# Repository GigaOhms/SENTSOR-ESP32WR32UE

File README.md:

# Learn KiCad Through a ESP32-micro Compact PCB Design Project

This repository is a learning resource to explore **PCB design with KiCad** through a practical project: a compact and powerful ESP32-based board.  
The reference for this project comes from [Sentsor Core ESP32-Micro](https://oshwlab.com/sentsor-project/sentsor-core-esp32-micro).

---

## Project Image

---

## Description

- **Super compact & powerful**, measured only 35.56x35.56mm (1400x1400mil) with 3x10P standard pitch 2.54mm (100mil) pinout, packing all the onboard features.  
- **ESP32-WROOM-32UE**, comes with latest ECO V3 Dual Core 32-bit LX6 microprocessor with clock up to 240MHz, ULP co-processor, 520kB SRAM, 16MB flash.  
- **802.11b/g/n WiFi Connectivity**, support mode STA/AP/STA+AP mode with external antenna using U.FL/IPEX connector allowing the board to be installed inside the enclosure without worrying transceiver signal quality.  
- **Bluetooth 4.2 Connectivity**, support classic bluetooth and Low Energy (LE) protocol.  
- **CP2104 UART to USB Bridge**, full-speed programmer & data port with auto-reset trigger using DTR and RTS line.  
- **DS3231M RTC**, extremely accurate ±5ppm RTC with alarm trigger capability and onboard MS621FE rechargeable backup battery. Connected via I2C at address 0x68.  
- **Battery Powered**, run SENTSOR board everywhere without power supply issue with 1-cell Lithium Ion/Polymer battery via JST-PH connector.  
- **CN3165 Battery Charger**, solar-powered and USB-compatible Lithium Ion/Polymer charger with on-chip adaptive charging current for wide range of input power scenario.  
- **DW01A Battery Protection**, battery usage protection against over-charge, over-discharge, over-current, and short circuit.  
- **BQ27441-G1 Battery Fuel Gauge**, accurately monitor your battery Relative State of Charge (RSOC).  
- **RT9078 & RT9013 LDO**, dual low quiescent current LDO design providing configurable +3.3V power rail up to 800mA.  
- **Super Low Power**, measured sleep mode power consumption down to XuW (XuA XV at VBAT pin, LDO2 off).  
- **Built-in LED/RGB**, single color active-low LED connected to pin IO2, and 4xSK6812 addressable RGB LED connected to pin IO4. SK6812 data out is exposed so you can chain it up with the rest of the LED circuit.  
- **MicroSD socket**, connected via SPI with slave select (SS) at pin IO5.  
- **22 pin GPIO** @3V3 level, 3xUART, 2xSPI, 2xI2C, 2xI2S, 12bit ADC, 8bit DAC, hall-effect sensing, capacitive sensing, JTAG debug, etc.  
  Please see pinout poster/schematic file for more information.  

---

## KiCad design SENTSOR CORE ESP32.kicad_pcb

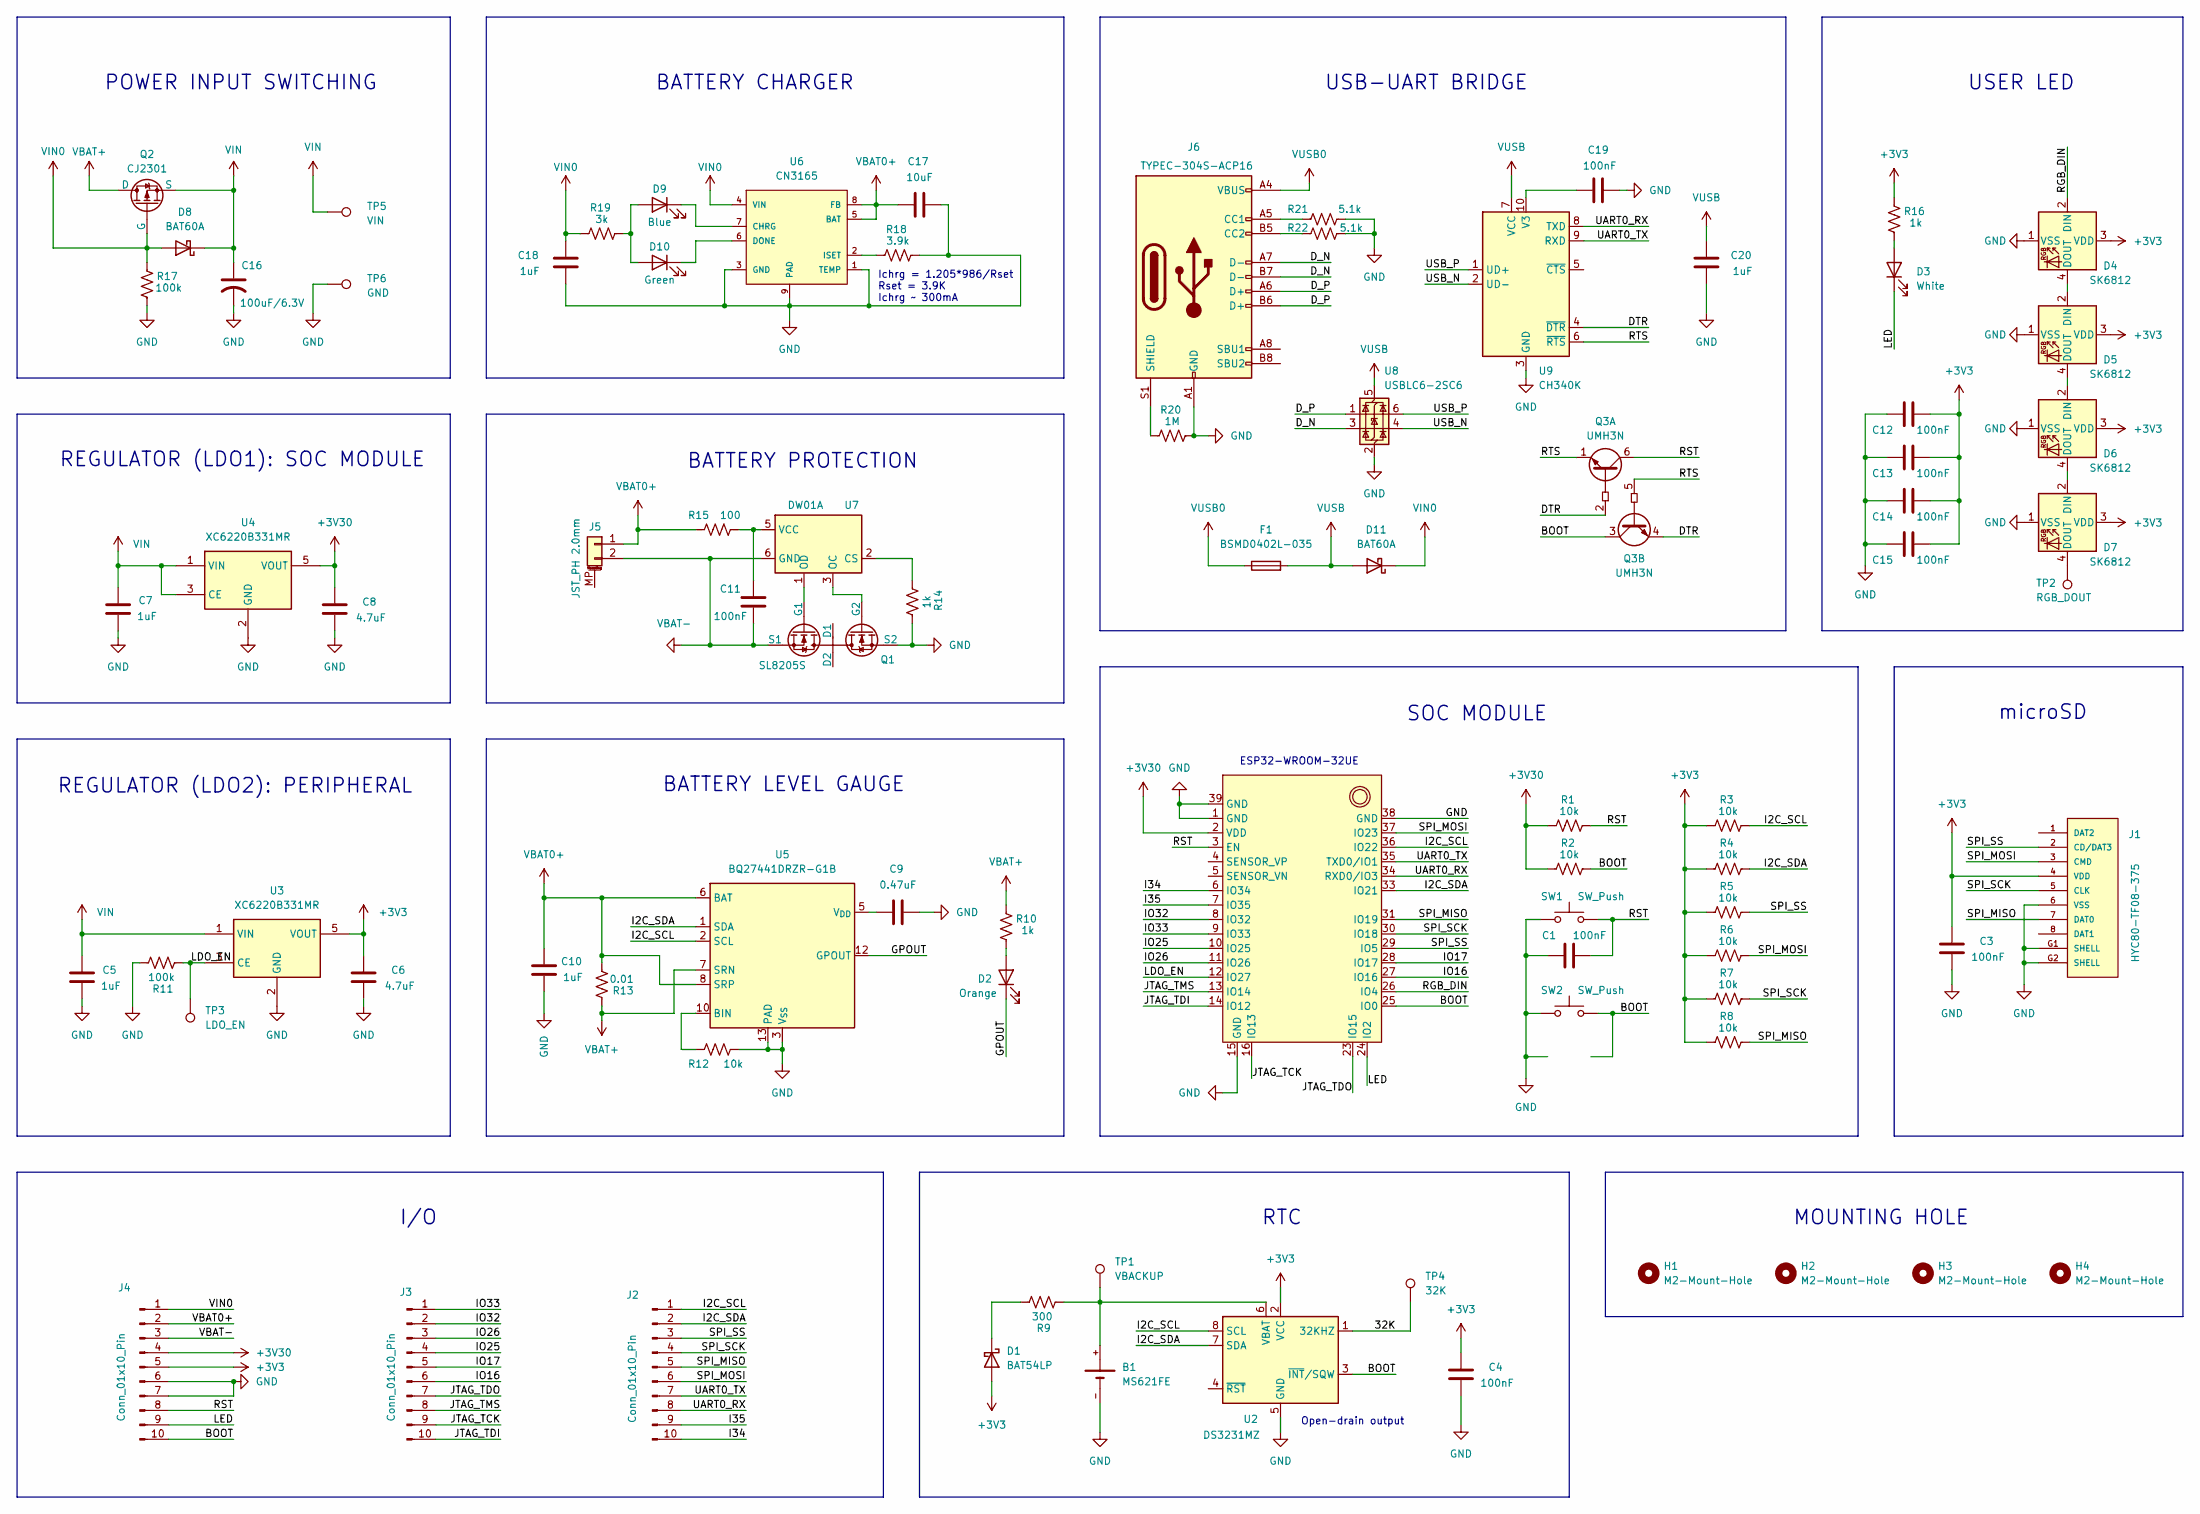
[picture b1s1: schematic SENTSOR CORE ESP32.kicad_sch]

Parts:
B1: MS621FE; BAT_MS621FE-SMD
C1, C3, C11, C12, C13, C14, C15, C19: 100nF; C_0402_1005Metric_Pad0.74x0.62mm_HandSolder
C4: 100nF; C_0402_1005Metric
C5, C7, C10, C20: 1uF; C_0402_1005Metric_Pad0.74x0.62mm_HandSolder
C6, C8: 4.7uF; C_0402_1005Metric_Pad0.74x0.62mm_HandSolder
C9: 0.47uF; C_0402_1005Metric_Pad0.74x0.62mm_HandSolder
C16: 100uF/6.3V; CP_EIA-3528-12_Kemet-T_HandSolder
C17: 10uF; C_0603_1608Metric
C18: 1uF; C_0402_1005Metric
D1: BAT54LP; D_0402_1005Metric_Pad0.77x0.64mm_HandSolder
D2: Orange; LED_0402_1005Metric_Pad0.77x0.64mm_HandSolder
D3: White; LED_0402_1005Metric_Pad0.77x0.64mm_HandSolder
D4, D5, D6, D7: SK6812; LED_SK6812_EC20_20x20mm
D8, D11: BAT60A; D_SOD-323_HandSoldering
D9: Blue; LED_0402_1005Metric_Pad0.77x0.64mm_HandSolder
D10: Green; LED_0402_1005Metric_Pad0.77x0.64mm_HandSolder
F1: BSMD0402L-035; Fuse_0402_1005Metric_Pad0.77x0.64mm_HandSolder
H1, H2, H3, H4: M2-Mount-Hole; MountingHole_2.2mm_M2
J1: HYC80-TF08-375; microSD_CARD_HYC80-TF08-xxx
J2, J3, J4: Conn_01x10_Pin; PinHeader_1x10_P2.54mm_Vertical
J5: JST_PH 2.0mm; JST_PH_S2B-PH-SM4-TB_1x02-1MP_P2.00mm_Horizontal
J6: TYPEC-304S-ACP16; USB_C_Receptacle_GCT_USB4110
Q1: SL8205S; SOT-23-6
Q2: CJ2301; SOT-23-3
Q3: UMH3N; SOT-363_SC-70-6
R1, R2, R3, R4, R5, R6, R7, R8: 10k; R_0402_1005Metric_Pad0.72x0.64mm_HandSolder
R9: 300; R_0402_1005Metric_Pad0.72x0.64mm_HandSolder
R10, R14, R16: 1k; R_0402_1005Metric_Pad0.72x0.64mm_HandSolder
R11, R17: 100k; R_0402_1005Metric_Pad0.72x0.64mm_HandSolder
R12: 10k; R_0402_1005Metric
R13: 0.01; R_0603_1608Metric_Pad0.98x0.95mm_HandSolder
R15: 100; R_0603_1608Metric_Pad0.98x0.95mm_HandSolder
R18: 3.9k; R_0603_1608Metric
R19: 3k; R_0402_1005Metric_Pad0.72x0.64mm_HandSolder
R20: 1M; R_0603_1608Metric
R21, R22: 5.1k; R_0402_1005Metric_Pad0.72x0.64mm_HandSolder
SW1, SW2: SW_Push; SW_2P_TS-1088-AR02016 3x4x2.5mm
TP1: VBACKUP; TestPoint_Pad_D0.7mm
TP2: RGB_DOUT; TestPoint_Pad_D0.7mm
TP3: LDO_EN; TestPoint_Pad_D0.7mm
TP4: 32K; TestPoint_Pad_D0.7mm
TP5: VIN; TestPoint_Pad_D0.7mm
TP6: GND; TestPoint_Pad_D0.7mm
U1: ESP32-WROOM-32UE
U2: DS3231MZ; SOIC-8_3.9x4.9mm_P1.27mm
U3, U4: XC6220B331MR; SOT-23-5
U5: BQ27441DRZR-G1B; Texas_S-PDSO-N12
U6: CN3165; DFN-8-1EP_3x3mm_P0.5mm_EP1.65x2.38mm_ThermalVias
U7: DW01A; SOT-23-6
U8: USBLC6-2SC6; SOT-23-6
U9: CH340K; SSOP-10-1EP_3.9x4.9mm_P1mm_EP2.1x3.3mm

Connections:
+3V3: C3.2, C4.2, C6.2, C12.2, C13.2, C14.2, C15.2, D1.2 (A), D4.3 (VDD), D5.3 (VDD), D6.3 (VDD), D7.3 (VDD), J1.4 (VDD), J4.5, R3.1, R4.1, R5.1, R6.1, R7.1, R8.1, R16.1, U2.2 (VCC), U3.5 (VOUT)
+3V30: C8.2, J4.4, R1.1, R2.1, U1.2 (VDD), U4.5 (VOUT)
/32K: TP4.1, U2.1 (32KHZ)
/BOOT: J4.10, Q3.3 (C2), R2.2, SW2.2, U1.25 (IO0), U2.3 (~INT/SQW)
/DTR: Q3.2 (B1), Q3.4 (E2), U9.4 (~DTR)
/D_N: J6.A7 (D-), J6.B7 (D-), U8.3 (I/O2)
/D_P: J6.A6 (D+), J6.B6 (D+), U8.1 (I/O1)
/GPOUT: D2.1 (K), U5.12 (GPOUT)
/I2C_SCL: J2.1, R3.2, U1.36 (IO22), U2.8 (SCL), U5.2 (SCL)
/I2C_SDA: J2.2, R4.2, U1.33 (IO21), U2.7 (SDA), U5.1 (SDA)
/I34: J2.10, U1.6 (IO34)
/I35: J2.9, U1.7 (IO35)
/IO16: J3.6, U1.27 (IO16)
/IO17: J3.5, U1.28 (IO17)
/IO25: J3.4, U1.10 (IO25)
/IO26: J3.3, U1.11 (IO26)
/IO32: J3.2, U1.8 (IO32)
/IO33: J3.1, U1.9 (IO33)
/JTAG_TCK: J3.9, U1.16 (IO13)
/JTAG_TDI: J3.10, U1.14 (IO12)
/JTAG_TDO: J3.7, U1.23 (IO15)
/JTAG_TMS: J3.8, U1.13 (IO14)
/LDO_EN: R11.1, TP3.1, U1.12 (IO27), U3.3 (CE)
/LED: D3.1 (K), J4.9, U1.24 (IO2)
/RGB_DIN: D4.2 (DIN), U1.26 (IO4)
/RST: C1.2, J4.8, Q3.6 (C1), R1.2, SW1.2, U1.3 (EN)
/RTS: Q3.1 (E1), Q3.5 (B2), U9.6 (~RTS)
/SPI_MISO: J1.7 (DAT0), J2.5, R8.2, U1.31 (IO19)
/SPI_MOSI: J1.3 (CMD), J2.6, R6.2, U1.37 (IO23)
/SPI_SCK: J1.5 (CLK), J2.4, R7.2, U1.30 (IO18)
/SPI_SS: J1.2 (CD/DAT3), J2.3, R5.2, U1.29 (IO5)
/UART0_RX: J2.8, U1.34 (RXD0/IO3), U9.8 (TXD)
/UART0_TX: J2.7, U1.35 (TXD0/IO1), U9.9 (RXD)
/USB_N: U8.4 (I/O2), U9.2 (UD-)
/USB_P: U8.6 (I/O1), U9.1 (UD+)
GND: B1.-, C1.1, C3.1, C4.1, C5.1, C6.1, C7.1, C8.1, C9.1, C10.1, C12.1, C13.1, C14.1, C15.1, C16.2, C17.1, C18.2, C19.2, C20.1, D4.1 (VSS), D5.1 (VSS), D6.1 (VSS), D7.1 (VSS), J1.6 (VSS), J1.G1 (SHELL), J1.G2 (SHELL), J4.6, J4.7, J6.A1 (GND), J6.A12 (GND), J6.B1 (GND), J6.B12 (GND), Q1.3 (S2), R11.2, R12.1, R14.2, R17.2, R18.2, R20.2, R21.2, R22.2, SW1.1, SW2.1, TP6.1, U1.1 (GND), U1.15 (GND), U1.38 (GND), U1.39 (GND), U2.5 (GND), U3.2 (GND), U4.2 (GND), U5.3 (V_{SS}), U5.13 (PAD), U6.1 (TEMP), U6.3 (GND), U6.9 (PAD), U8.2 (GND), U9.3 (GND), U9.11 (GND)
unnamed: D1.1 (K), R9.2
unnamed: D2.2 (A), R10.2
unnamed: D3.2 (A), R16.2
unnamed: D4.4 (DOUT), D5.2 (DIN)
unnamed: D5.4 (DOUT), D6.2 (DIN)
unnamed: D6.4 (DOUT), D7.2 (DIN)
unnamed: D7.4 (DOUT), TP2.1
unnamed: D9.1 (K), U6.7 (CHRG)
unnamed: D9.2 (A), D10.2 (A), R19.2
unnamed: D10.1 (K), U6.6 (DONE)
unnamed: J6.A5 (CC1), R21.1
unnamed: J6.B5 (CC2), R22.1
unnamed: J6.S1 (SHIELD), R20.1
unnamed: Q1.6 (G1), U7.1 (OD)
unnamed: Q1.4 (G2), U7.3 (OC)
unnamed: B1.+, R9.1, TP1.1, U2.6 (VBAT)
unnamed: R12.2, U5.10 (BIN)
unnamed: C9.2, U5.5 (V_{DD})
unnamed: R18.1, U6.2 (ISET)
unnamed: R14.1, U7.2 (CS)
unnamed: C11.2, R15.2, U7.5 (VCC)
unnamed: C19.1, U9.10 (V3)
VBAT0+: C10.2, C17.2, J4.2, J5.1, R13.1, R15.1, U5.6 (BAT), U5.8 (SRP), U6.5 (BAT), U6.8 (FB)
VBAT+: Q2.3 (D), R10.1, R13.2, U5.7 (SRN)
VBAT-: C11.1, J4.3, J5.2, Q1.1 (S1), U7.6 (GND)
VIN: C5.2, C7.2, C16.1, D8.1 (K), Q2.2 (S), TP5.1, U3.1 (VIN), U4.1 (VIN), U4.3 (CE)
VIN0: C18.1, D8.2 (A), D11.1 (K), J4.1, Q2.1 (G), R17.1, R19.1, U6.4 (VIN)
VUSB: C20.2, D11.2 (A), F1.2, U8.5 (VBUS), U9.7 (VCC)
VUSB0: F1.1, J6.A4 (VBUS), J6.A9 (VBUS), J6.B4 (VBUS), J6.B9 (VBUS)

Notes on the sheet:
RTC
Open-drain output
ESP32-WROOM-32UE
SOC MODULE
MOUNTING HOLE
BATTERY LEVEL GAUGE
USER LED
REGULATOR (LDO2): PERIPHERAL
microSD
USB-UART BRIDGE
I/O
BATTERY PROTECTION
Ichrg = 1.205*986/Rset Rset = 3.9K Ichrg ~ 300mA
POWER INPUT SWITCHING
REGULATOR (LDO1): SOC MODULE
BATTERY CHARGER

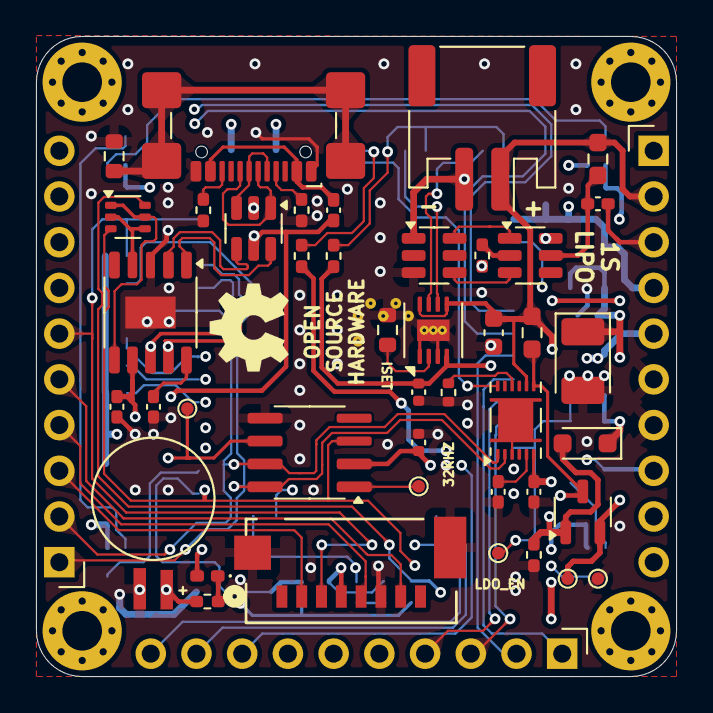
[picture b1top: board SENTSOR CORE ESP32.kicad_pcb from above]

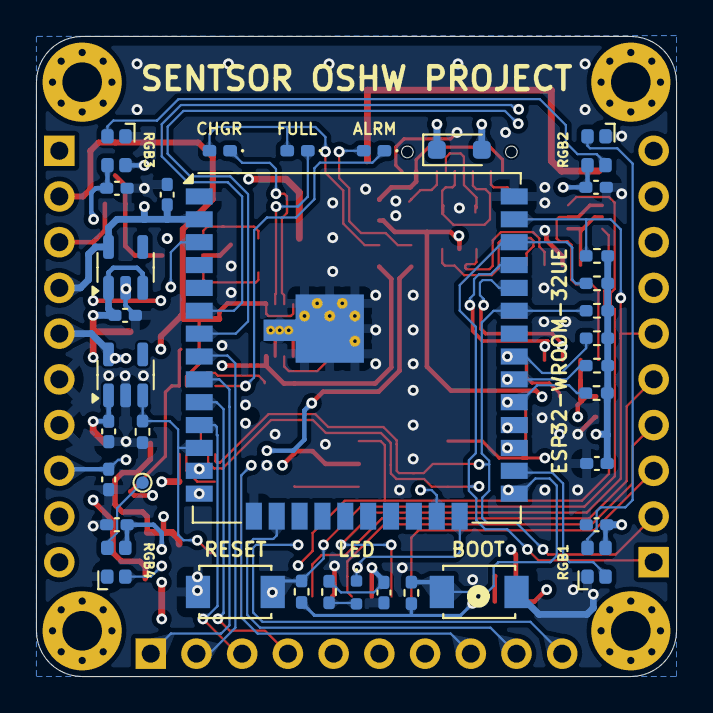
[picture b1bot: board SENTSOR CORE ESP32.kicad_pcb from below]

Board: 4 copper layers, 35.6 x 35.6 mm, 84 parts (35 on the bottom side), 65 nets.

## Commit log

2025-08-14 first done SCH
2025-08-16 add board cut line
2025-08-17 add board layout
2025-08-21 add board layout 85%
2025-08-21 add board layout 90%
2025-08-22 add board layout 100% first
2025-08-22 add readme
